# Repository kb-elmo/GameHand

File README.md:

# GameHand

[![CC BY-NC-SA 4.0][cc-by-nc-sa-shield]][cc-by-nc-sa] 

### Left-hand gaming keypad with a 3D printed case

---

[Case files](case/)

[KiCAD PCB files](pcb/)

[Gerbers for PCB production](pcb/gerbers/)

[JLCPCB BOM](pcb/fab/GameHand_bom_jlc.csv)

[JLCPCB CPL](pcb/fab/GameHand_cpl_jlc.csv)

---

This work is licensed under a
[Creative Commons Attribution-NonCommercial-ShareAlike 4.0 International License][cc-by-nc-sa].

[![CC BY-NC-SA 4.0][cc-by-nc-sa-image]][cc-by-nc-sa]

[cc-by-nc-sa]: http://creativecommons.org/licenses/by-nc-sa/4.0/
[cc-by-nc-sa-image]: https://licensebuttons.net/l/by-nc-sa/4.0/88x31.png
[cc-by-nc-sa-shield]: https://img.shields.io/badge/License-CC%20BY--NC--SA%204.0-lightgrey.svg

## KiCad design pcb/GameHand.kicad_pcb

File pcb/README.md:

# GameHand PCB

---

The GameHand PCB is powered by an ATmega32u2 MCU and has basic ESD and overvoltage protection.  

With the firmware files in this repo the board is capable of full NKRO and 1000 Hz USB polling.

---

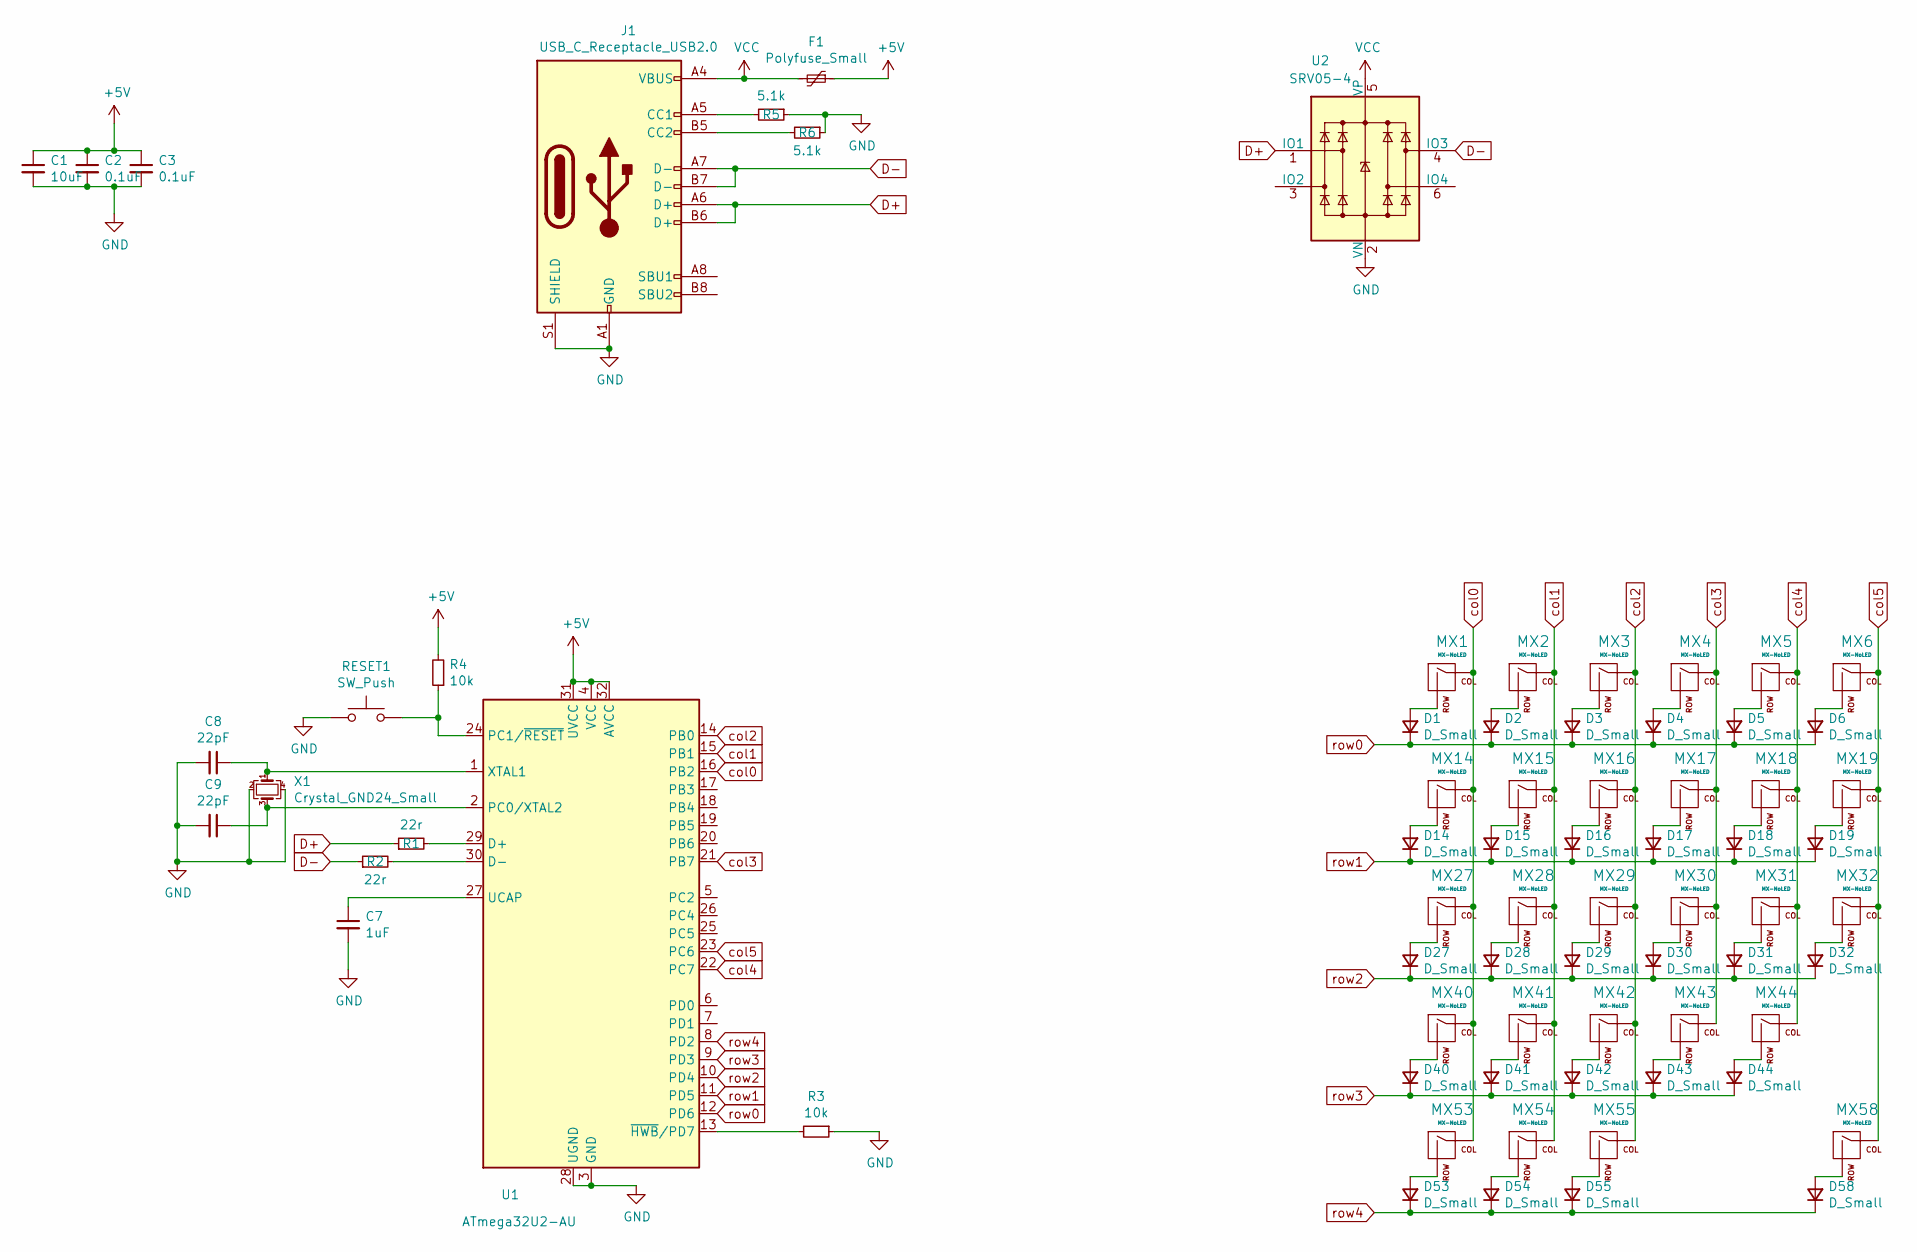
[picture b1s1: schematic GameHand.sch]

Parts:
C1: 10uF; C_0805_2012Metric; LCSC C91245
C2, C3: 0.1uF; C_0805_2012Metric; LCSC C49678
C7: 1uF; C_0805_2012Metric; LCSC C28323
C8, C9: 22pF; C_0805_2012Metric; LCSC C1804
D1, D2, D3, D4, D5, D6, D14, D15, D16, D17, D18, D19, D27, D28, D29, D30, D31, D32, D40, D41, D42, D43, D44, D53, D54, D55, D58: D_Small; D_SOD-123; LCSC C81598
F1: Polyfuse_Small; Fuse_1206_3216Metric; LCSC C69688
J1: USB_C_Receptacle_USB2.0; USB_C_Receptacle_HRO_TYPE-C-31-M-12
MX1, MX2, MX3, MX4, MX5, MX6, MX14, MX15, MX16, MX17, MX18, MX19, MX28, MX29, MX30, MX31, MX32, MX41, MX42, MX43, MX44: MX-NoLED; MXOnly-1U-NoLED
MX27: MX-NoLED; MXOnly-1.25U-NoLED
MX40: MX-NoLED; MXOnly-1.75U-NoLED
MX53, MX54, MX55: MX-NoLED; MXOnly-1.5U-NoLED
MX58: MX-NoLED; MXOnly-2.75U-ReversedStabilizers-NoLED
R1, R2: 22r; R_0805_2012Metric; LCSC C17561
R3, R4: 10k; R_0805_2012Metric; LCSC C17414
R5, R6: 5.1k; R_0805_2012Metric; LCSC C27834
RESET1: SW_Push; SW_SPST_TL3342; LCSC C318884
U1: ATmega32U2-AU; TQFP-32_7x7mm_P0.8mm
U2: SRV05-4; SOT-23-6; LCSC C85364
X1: Crystal_GND24_Small; Crystal_SMD_3225-4Pin_3.2x2.5mm; LCSC C13738

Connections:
+5V: C1.1, C2.1, C3.1, F1.1, R4.2, U1.4 (VCC), U1.31 (UVCC), U1.32 (AVCC)
D+: J1.A6 (D+), J1.B6 (D+), R1.1, U2.1 (IO1)
D-: J1.A7 (D-), J1.B7 (D-), R2.1, U2.4 (IO3)
GND: C1.2, C2.2, C3.2, C7.2, C8.2, C9.2, J1.A1 (GND), J1.A12 (GND), J1.B1 (GND), J1.B12 (GND), J1.S1 (SHIELD), R3.1, R5.1, R6.1, RESET1.1, U1.3 (GND), U1.28 (UGND), U2.2 (VN), X1.2, X1.4; also elsewhere on the board
unnamed: C7.1, U1.27 (UCAP)
unnamed: C8.1, U1.1 (XTAL1), X1.1
unnamed: C9.1, U1.2 (PC0/XTAL2), X1.3
unnamed: D1.2 (A), MX1.2 (ROW)
unnamed: D2.2 (A), MX2.2 (ROW)
unnamed: D3.2 (A), MX3.2 (ROW)
unnamed: D4.2 (A), MX4.2 (ROW)
unnamed: D5.2 (A), MX5.2 (ROW)
unnamed: D6.2 (A), MX6.2 (ROW)
unnamed: D14.2 (A), MX14.2 (ROW)
unnamed: D15.2 (A), MX15.2 (ROW)
unnamed: D16.2 (A), MX16.2 (ROW)
unnamed: D17.2 (A), MX17.2 (ROW)
unnamed: D18.2 (A), MX18.2 (ROW)
unnamed: D19.2 (A), MX19.2 (ROW)
unnamed: D27.2 (A), MX27.2 (ROW)
unnamed: D28.2 (A), MX28.2 (ROW)
unnamed: D29.2 (A), MX29.2 (ROW)
unnamed: D30.2 (A), MX30.2 (ROW)
unnamed: D31.2 (A), MX31.2 (ROW)
unnamed: D32.2 (A), MX32.2 (ROW)
unnamed: D40.2 (A), MX40.2 (ROW)
unnamed: D41.2 (A), MX41.2 (ROW)
unnamed: D42.2 (A), MX42.2 (ROW)
unnamed: D43.2 (A), MX43.2 (ROW)
unnamed: D44.2 (A), MX44.2 (ROW)
unnamed: D53.2 (A), MX53.2 (ROW)
unnamed: D54.2 (A), MX54.2 (ROW)
unnamed: D55.2 (A), MX55.2 (ROW)
unnamed: D58.2 (A), MX58.2 (ROW)
unnamed: J1.A5 (CC1), R5.2
unnamed: J1.B5 (CC2), R6.2
unnamed: R1.2, U1.29 (D+)
unnamed: R2.2, U1.30 (D-)
unnamed: R3.2, U1.13 (~HWB~/PD7)
unnamed 41: R4.1, RESET1.2, U1.24 (PC1/~RESET); also elsewhere on the board
VCC: F1.2, J1.A4 (VBUS), J1.A9 (VBUS), J1.B4 (VBUS), J1.B9 (VBUS), U2.5 (VP)
col0: MX1.1 (COL), MX14.1 (COL), MX27.1 (COL), MX40.1 (COL), MX53.1 (COL), U1.16 (PB2)
col1: MX2.1 (COL), MX15.1 (COL), MX28.1 (COL), MX41.1 (COL), MX54.1 (COL), U1.15 (PB1)
col2: MX3.1 (COL), MX16.1 (COL), MX29.1 (COL), MX42.1 (COL), MX55.1 (COL), U1.14 (PB0)
col3: MX4.1 (COL), MX17.1 (COL), MX30.1 (COL), MX43.1 (COL), U1.21 (PB7)
col4: MX5.1 (COL), MX18.1 (COL), MX31.1 (COL), MX44.1 (COL), U1.22 (PC7)
col5: MX6.1 (COL), MX19.1 (COL), MX32.1 (COL), MX58.1 (COL), U1.23 (PC6)
row0: D1.1 (K), D2.1 (K), D3.1 (K), D4.1 (K), D5.1 (K), D6.1 (K), U1.12 (PD6)
row1: D14.1 (K), D15.1 (K), D16.1 (K), D17.1 (K), D18.1 (K), D19.1 (K), U1.11 (PD5)
row2: D27.1 (K), D28.1 (K), D29.1 (K), D30.1 (K), D31.1 (K), D32.1 (K), U1.10 (PD4)
row3: D40.1 (K), D41.1 (K), D42.1 (K), D43.1 (K), D44.1 (K), U1.9 (PD3)
row4: D53.1 (K), D54.1 (K), D55.1 (K), D58.1 (K), U1.8 (PD2)

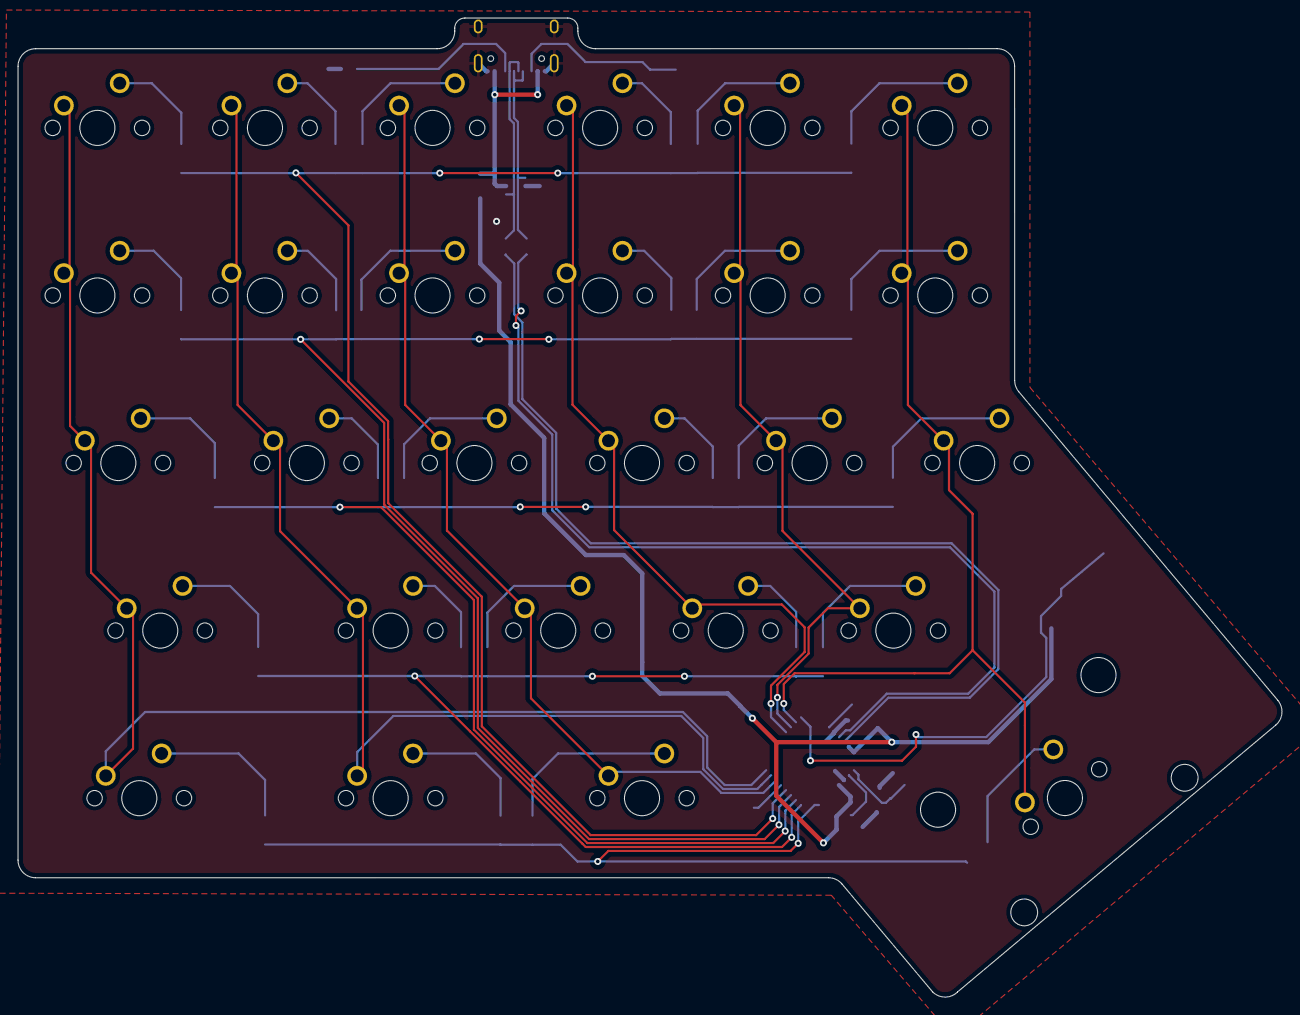
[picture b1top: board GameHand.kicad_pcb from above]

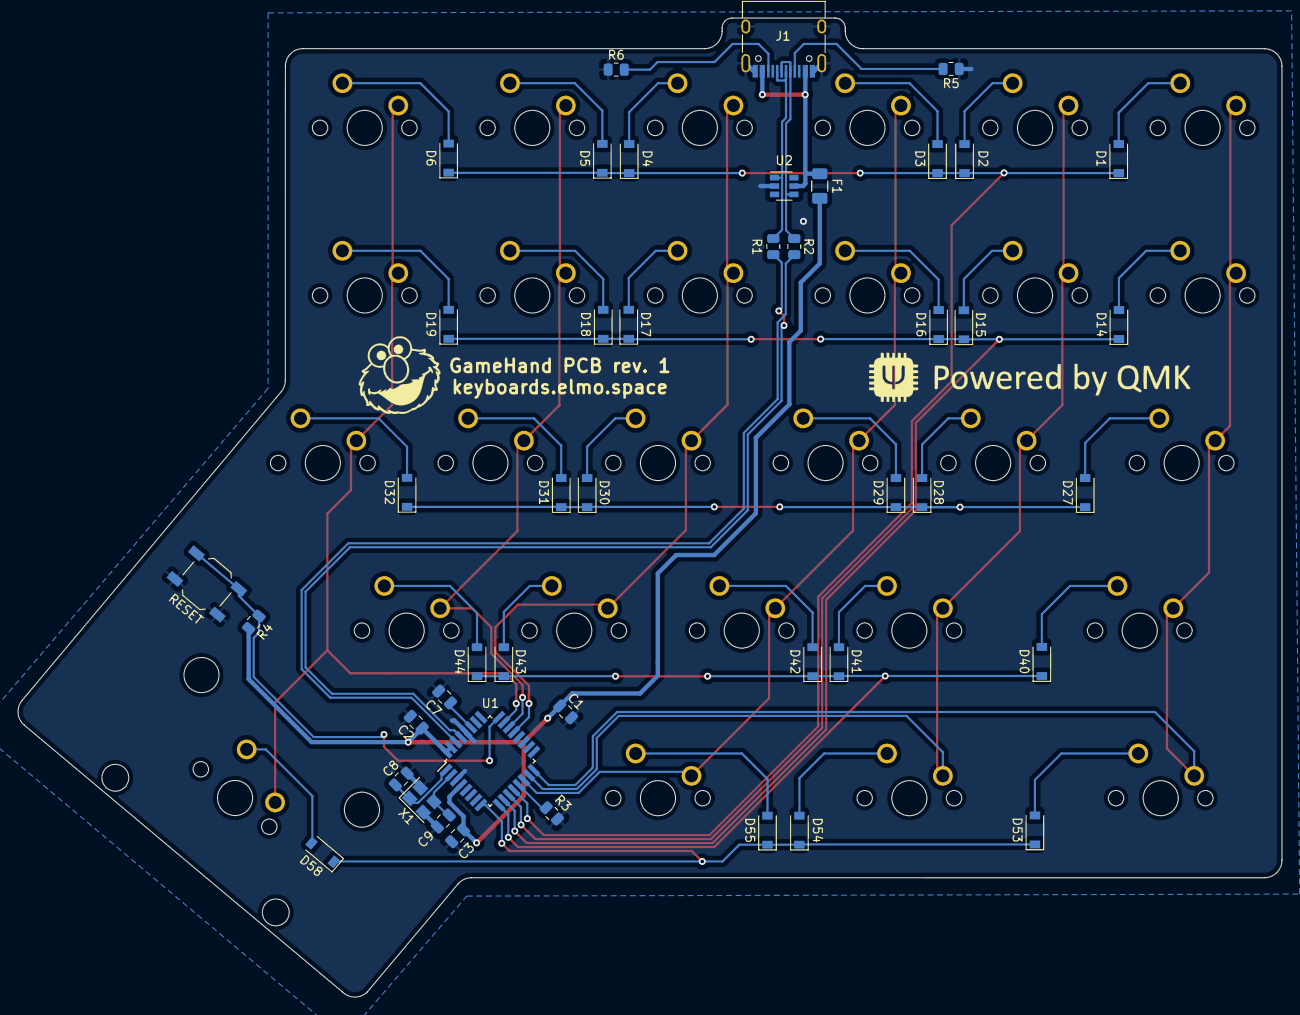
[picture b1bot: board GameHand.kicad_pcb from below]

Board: 2 copper layers, 143.7 x 111.3 mm, 72 parts (45 on the bottom side), 52 nets.

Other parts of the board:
RESET: SW_Push; SW_SPST_TL3342

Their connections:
GND: RESET.1; also elsewhere on the board
unnamed 41: RESET.2; also elsewhere on the board

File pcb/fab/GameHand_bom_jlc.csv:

"Comment","Designator","Footprint","LCSC Part #"
"10uF","C1","C_0805_2012Metric","C91245"
"0.1uF","C2,C3","C_0805_2012Metric","C49678"
"1uF","C7","C_0805_2012Metric","C28323"
"22pF","C8,C9","C_0805_2012Metric","C1804"
"D_Small","D1,D2,D3,D4,D5,D6,D14,D15,D16,D17,D18,D19,D27,D28,D29,D30,D31,D32,D40,D41,D42,D43,D44,D53,D54,D58,D55","D_SOD-123","C81598"
"Polyfuse_Small","F1","Fuse_1206_3216Metric","C69688"
"22r","R1,R2","R_0805_2012Metric","C17561"
"10k","R3,R4","R_0805_2012Metric","C17414"
"5.1k","R5,R6","R_0805_2012Metric","C27834"
"SW_Push","RESET","SW_SPST_TL3342","C318884"
"SRV05-4","U2","SOT-23-6","C85364"
"Crystal_GND24_Small","X1","Crystal_SMD_3225-4Pin_3.2x2.5mm","C13738"

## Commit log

2021-07-09 add PCB files
2021-07-09 remove submodule files
2021-07-09 add submodule
2021-07-09 change readme layout
2021-07-10 update gerbers
2021-07-10 fix keymap
2021-07-10 update keymap
2021-07-10 remove unused corner cutouts
2021-07-10 update drillfiles
